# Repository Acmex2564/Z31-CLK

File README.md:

# Z31-CLK
Replacement clock for Z31

Z31 GL clocks are a a 4-digit VFD driven by a HD44013 MCU. 

For no good reason I intend to replace all parts except the VFD, which uniquely operates directly DC voltage through a couple current limiting resistors and protection diodes. 

Replacement clock will source time from a new TCU design, and communicate over CAN, allowing it to serve as an interface to other accessories I've installed.

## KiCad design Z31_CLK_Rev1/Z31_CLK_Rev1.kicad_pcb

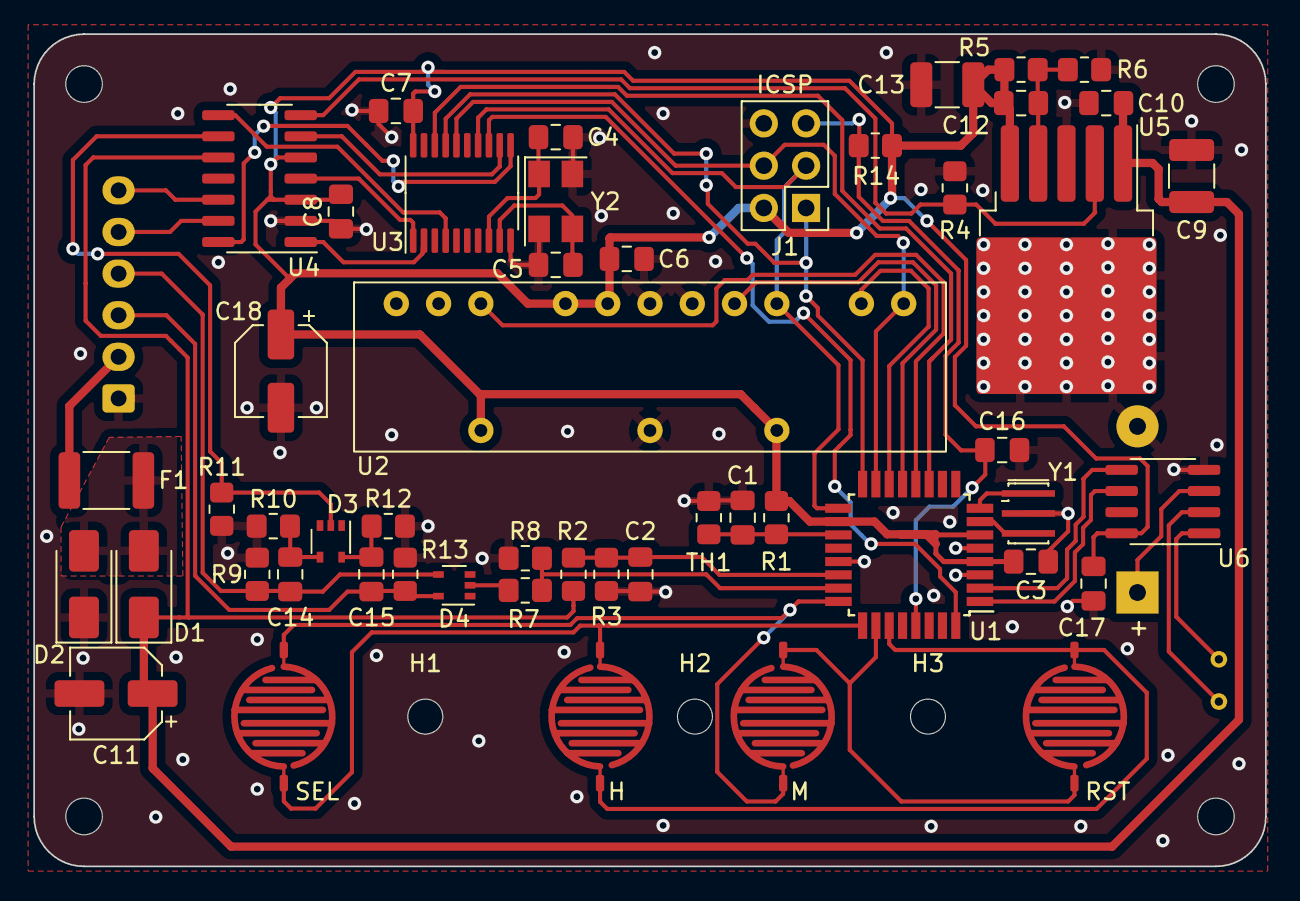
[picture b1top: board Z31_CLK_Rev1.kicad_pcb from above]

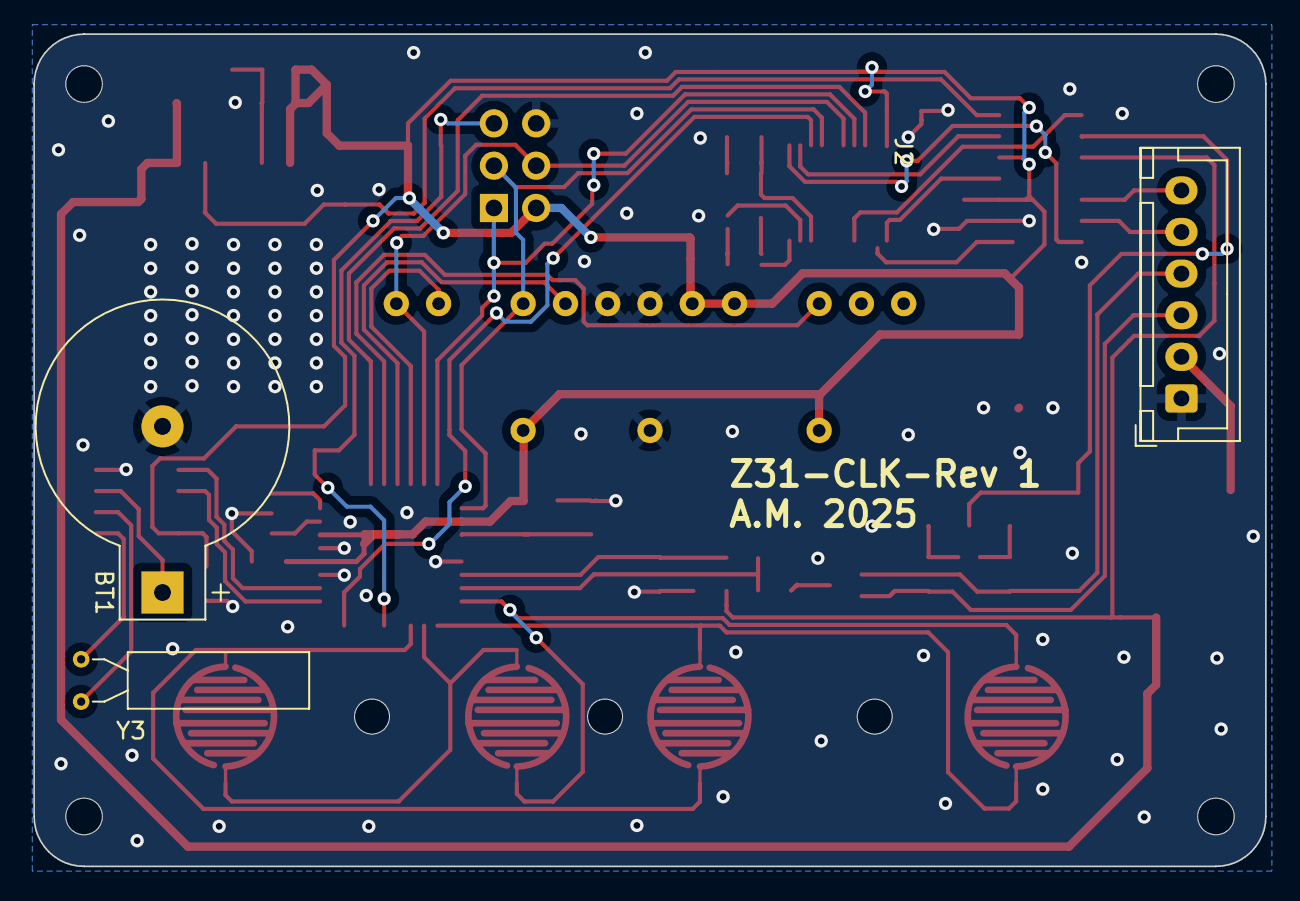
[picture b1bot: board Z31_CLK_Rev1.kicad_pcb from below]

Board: 2 copper layers, 74.0 x 50.0 mm, 61 parts (3 on the bottom side), 45 nets.

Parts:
BT1: 3V; BatteryHolder_Keystone_500
C1, C2, C6, C7, C8, C10, C16, C17: 100nF; C_0805_2012Metric_Pad1.18x1.45mm_HandSolder
C3, C14, C15: 100n; C_0805_2012Metric_Pad1.18x1.45mm_HandSolder
C4, C5: 10pF; C_0805_2012Metric_Pad1.18x1.45mm_HandSolder
C9: 1u; C_1210_3225Metric_Pad1.33x2.70mm_HandSolder
C11, C18: 22uF; CP_Elec_5x5.7
C12: N/A; C_0805_2012Metric_Pad1.18x1.45mm_HandSolder
C13: yes; C_1210_3225Metric_Pad1.33x2.70mm_HandSolder
D1: D_Schottky; D_SMA
D2: SMAJ18CAQ-13-F; D_SMA
D3, D4: MMBD4448HCQW; SOT-353_SC-70-5
F1: Polyfuse; Fuse_1812_4532Metric_Pad1.30x3.40mm_HandSolder
H1, H2, H3: MountingHole; MountingHole_2.1mm
H4, H5, H6, H7: MountingHole; MountingHole_2.2mm_M2_DIN965
J1: ICSP; PinHeader_2x03_P2.54mm_Vertical
J2: Conn_01x06_Male; JST_XH_B6B-XH-A_1x06_P2.50mm_Vertical
R1: 47K; R_0805_2012Metric_Pad1.20x1.40mm_HandSolder
R2, R3: R; R_0805_2012Metric_Pad1.20x1.40mm_HandSolder
R4, R7, R8, R9, R10, R11, R12, R13, R14: 10k; R_0805_2012Metric_Pad1.20x1.40mm_HandSolder
R5, R6: N/A; R_0805_2012Metric_Pad1.20x1.40mm_HandSolder
SW1: Select; membrane_button
SW2: Hour; membrane_button
SW3: Reset; membrane_button
SW4: Minute; membrane_button
TH1: NTC 47K; R_0805_2012Metric_Pad1.20x1.40mm_HandSolder
U1: ATMEGA328-AURCT-ND; TQFP-32_7x7mm_P0.8mm
U2: HCMS-291x
U3: MCP2515-xST; TSSOP-20_4.4x6.5mm_P0.65mm
U4: TJR1443; SO-14_3.9x8.65mm_P1.27mm
U5: NCV4276B; TO-263-5_TabPin3
U6: DS1307Z+; SOIC-8_3.9x4.9mm_P1.27mm
Y1: 16MHz; Resonator_SMD_Murata_CSTxExxV-3Pin_3.0x1.1mm_HandSoldering
Y2: 8MHz; Crystal_SMD_5032-4Pin_5.0x3.2mm
Y3: 32.768k; Crystal_AT310_D3.0mm_L10.0mm_Horizontal

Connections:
+5V: C3.1, C6.2, C7.2, C8.2, C12.1, C13.1, C17.2, C18.1, J1.2, R1.1, R5.1, R14.1, U1.4 (VCC), U1.6 (VCC), U1.18 (AVCC), U2.3 (V_{LED}), U2.10 (V_{LED}), U2.21 (SEL), U2.22 (V_{Logic}), U3.20 (VDD), U4.3 (Vcc), U4.5 (Vio), U5.5 (OUT), U6.8 (VCC)
+12V: C9.1, C10.1, C11.1, D1.1 (K), R2.1, U4.10 (Vbat), U5.1 (IN)
/+12V_ACC: C14.1, D4.4 (A), J2.4, R9.1
/+12V_CONST: F1.2, J2.2
/CANH: J2.5, U4.13 (CANH)
/CANL: J2.6, U4.12 (CANL)
/CAN_EN: U3.12 (~RX0BF), U4.6 (EN)
/CAN_ERR: U3.4 (~TX0RTS), U4.8 (~ERR)
/CAN_STB: U3.11 (~RX1BF), U4.14 (~STB_N)
/ILLUM: C15.1, D4.5 (A), J2.3, R13.1
/Key_1: SW3.2, SW4.2, U1.26 (PC3)
/Key_2: SW1.1, SW2.1, U1.25 (PC2)
/Key_A: SW1.2, SW3.1, U1.24 (PC1)
/Key_B: SW2.2, SW4.1, U1.27 (PC4)
/MODULE_TEMPERATURE: C1.1, R1.2, TH1.1, U1.19 (ADC6)
/MODULE_VOLTAGE: C2.1, R2.2, R3.1, U1.22 (ADC7)
/RS_DISP: U1.14 (PB2), U2.15 (RS)
/RXCAN: U3.2 (RXCAN), U4.1 (TXCAN)
/TXCAN: U3.1 (TXCAN), U4.4 (RXCAN)
/Wake_Pulse: D3.2 (K), R11.1, U4.9 (WAKE)
/Wake_Sense: R7.2, R8.1, U1.23 (PC0)
/~CS_CAN: U1.11 (PD7), U3.18 (~CS)
/~CS_DISP: U1.13 (PB1), U2.18 (~CE)
/~INH: R4.1, U4.7 (INH), U5.2 (INH)
/~RST_DISP: U1.12 (PB0), U2.24 (~RESET)
CAN_INT: U1.32 (PD2), U3.13 (~INT)
GND: BT1.2 (-), C1.2, C2.2, C3.2, C4.1, C5.1, C6.1, C7.1, C8.1, C9.2, C10.2, C11.2, C13.2, C16.1, C17.1, C18.2, D2.1 (A1), J1.6, J2.1, R3.2, R4.2, R6.2, R8.2, R9.2, R10.2, R11.2, R12.2, R13.2, TH1.2, U1.3 (GND), U1.5 (GND), U1.21 (GND), U2.7 (GND_{LED}), U2.19 (BLANK), U2.20 (GND_{Logic}), U3.10 (VSS), U4.2 (GND), U5.3 (GND), U6.4 (GND), Y1.2, Y2.2, Y2.4
MISO: J1.1, U1.16 (PB4), U3.17 (SO)
MOSI: J1.4, U1.15 (PB3), U2.14 (Data_In), U3.16 (SI)
unnamed: BT1.1 (+), U6.3 (VBAT)
unnamed: D1.2 (A), D2.2 (A2), F1.1
unnamed: C14.2, D3.4 (A), R10.1
unnamed: C15.2, D3.5 (A), R12.1
unnamed: D4.2 (K), R7.1
unnamed: U1.1 (PD3), U6.6 (SCL)
unnamed: U1.2 (PD4), U6.5 (SDA)
unnamed: U1.7 (XTAL1/PB6), Y1.3
unnamed: U1.8 (XTAL2/PB7), Y1.1
unnamed: C5.2, U3.9 (OSC1), Y2.3
unnamed: C4.2, U3.8 (OSC2), Y2.1
unnamed: C12.2, R5.2, R6.1, U5.4 (VA)
unnamed: U6.1 (X1), Y3.2
unnamed: U6.2 (X2), Y3.1
RESET: C16.2, J1.5, R14.2, U1.29 (~RESET/PC6)
SCK: J1.3, U1.17 (PB5), U2.17 (CLK), U3.14 (SCK)

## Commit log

2022-05-29 add code
2022-09-29 Catchup
2025-01-17 Feature-complete Z31-CLK-Rev1; some PCB layout cleanup may still be useful.
    Review pending.
2025-04-20 Finalize clock design
